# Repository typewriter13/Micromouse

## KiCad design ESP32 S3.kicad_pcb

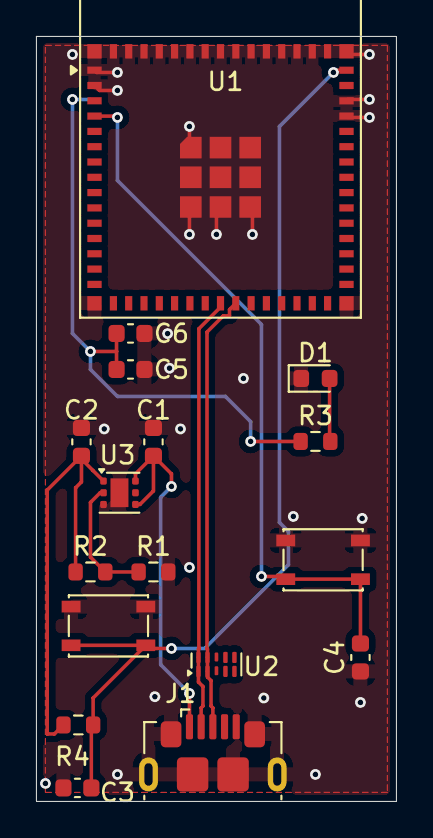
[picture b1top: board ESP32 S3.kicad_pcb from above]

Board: 2 copper layers, 20.0 x 42.5 mm, 17 parts (0 on the bottom side), 9 nets.

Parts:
C1, C2, C6: 10uF; C_0603_1608Metric
C3, C4, C5: 0.1uF; C_0603_1608Metric
D1: LED; LED_0603_1608Metric
J1: USB_B_Micro; USB_Micro-B_GCT_USB3076-30-A
R1: 200K; R_0603_1608Metric
R2: 1M; R_0603_1608Metric
R3: 5.1K; R_0603_1608Metric
R4: 10K; R_0603_1608Metric
SW1: RESET; SW_SPST_PTS810
SW2: BOOT; SW_SPST_PTS810
U1: ESP32-S3-MINI-1; ESP32-S2-MINI-1
U2: D3V3XA4B10LP; Diodes_UDFN-10_1x2.5mm_P0.5mm
U3: TLV75801PDRV; WSON-6-1EP_2x2mm_P0.65mm_EP1x1.6mm

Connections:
/3V3: C2.1, C5.2, C6.1, R2.1, R3.1, R4.1, U1.3 (3V3), U3.1 (OUT)
/5VUSB: C1.1, J1.1 (VBUS), U2.4, U2.7 (NC), U3.4 (EN), U3.6 (IN)
/ESP32_EN: C3.2, R4.2, SW1.2, U1.45 (EN)
/GPIOO: C4.2, SW2.2, U1.4 (IO0)
/USB_N: J1.2 (D-), U1.23 (USB_D-), U2.1, U2.10 (NC)
/USB_P: J1.3 (D+), U1.24 (USB_D+), U2.2, U2.9 (NC)
GND: C1.2, C2.2, C3.1, C4.1, C5.1, C6.2, D1.1 (K), J1.5 (GND), J1.SH (Shield), R1.2, SW1.1, SW2.1, U1.1 (GND), U1.2 (GND), U1.42 (GND), U1.43 (GND), U1.46 (GND), U1.47 (GND), U1.48 (GND), U1.49 (GND), U1.50 (GND), U1.51 (GND), U1.52 (GND), U1.53 (GND), U1.54 (GND), U1.55 (GND), U1.56 (GND), U1.57 (GND), U1.58 (GND), U1.59 (GND), U1.60 (GND), U1.61 (GND), U1.62 (GND), U1.63 (GND), U1.64 (GND), U1.65 (GND), U2.3 (VSS), U2.8 (VSS), U3.3 (GND), U3.7 (GND)
unnamed: D1.2 (A), R3.2
unnamed: R1.1, R2.2, U3.2 (FB)

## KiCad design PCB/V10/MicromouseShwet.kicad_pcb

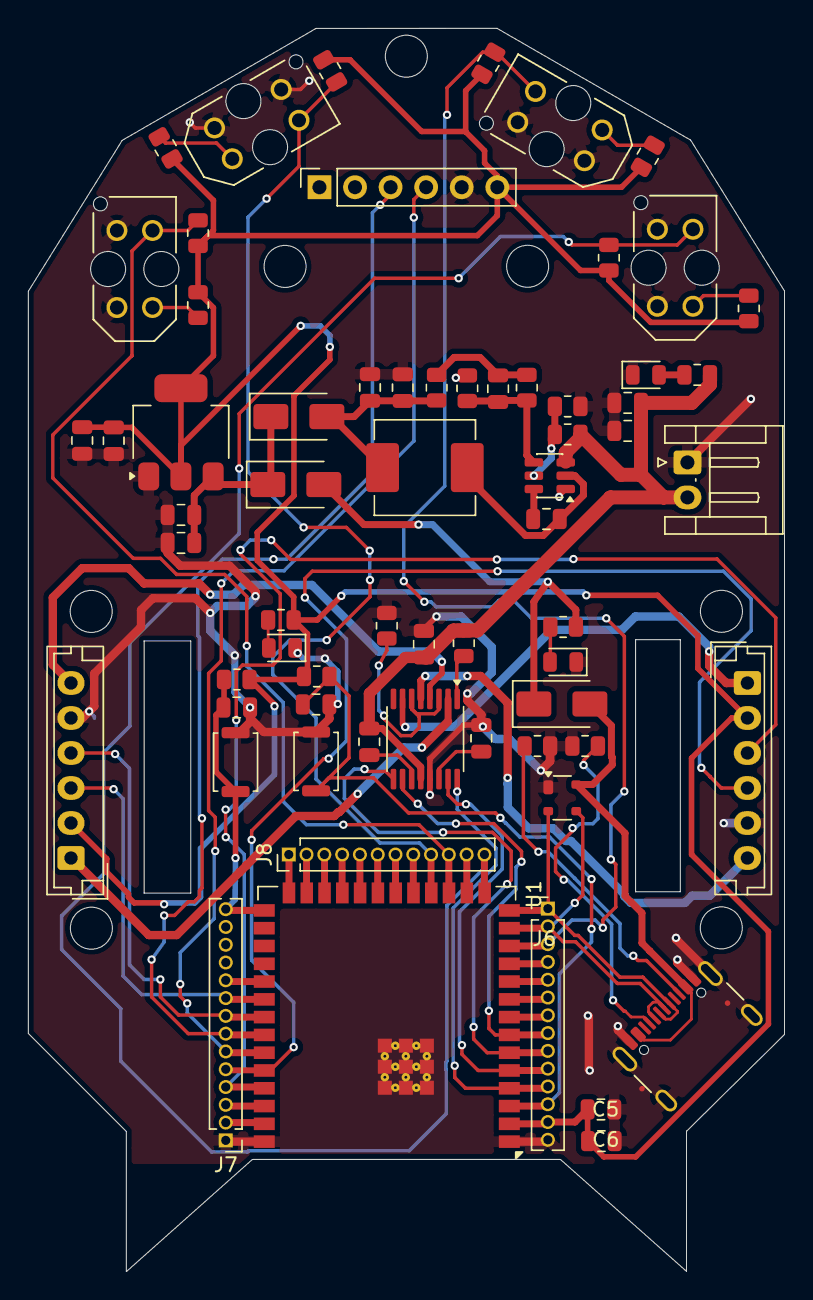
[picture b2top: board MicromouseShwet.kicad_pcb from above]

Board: 2 copper layers, 54.0 x 88.8 mm, 65 parts (0 on the bottom side), 63 nets.

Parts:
C1: 0.01uF; C_0805_2012Metric
C2: 2.2uF; C_0805_2012Metric
C3, C6, C8, C14: 10uF; C_0805_2012Metric
C4, C5, C7, C9, C10, C15, C17: 0.1uF; C_0805_2012Metric
C11, C12, C16: 22uF; C_0805_2012Metric
C13: 75pF; C_0805_2012Metric
D7: SP0503BAHT; SOT-143
D14, D17, D18: LED; LED_0805_2012Metric
D16, D19, D20: SS14; D_SMA
J1: ToF Female Socket; PinSocket_1x06_P2.54mm_Vertical
J2: Screw_Terminal_01x02; JST_EH_S2B-EH_1x02_P2.50mm_Horizontal
J5: USB_C_Receptacle_USB2.0_16P; USB_C_Receptacle_GCT_USB4105-xx-A_16P_TopMnt_Horizontal
J6, J7: Conn_01x14_Pin; PinHeader_1x14_P1.27mm_Vertical
J8: Conn_01x12_Pin; PinHeader_1x12_P1.27mm_Vertical
J10, J11: Conn_01x06_Pin; JST_EH_B6B-EH-A_1x06_P2.50mm_Vertical
L1: 10uH; L_Sunlord_MWSA0603S
R1: 200mOhm; R_0805_2012Metric
R2, R4, R9, R11: 4.7k; R_0805_2012Metric
R3, R5, R10, R12: 150R; R_0805_2012Metric
R6, R8: 5.1K; R_0805_2012Metric
R7, R20: 10K; R_0805_2012Metric
R13: 511K; R_0805_2012Metric
R14: 105K; R_0805_2012Metric
R15: 49.9K; R_0805_2012Metric
R16, R25, R26: 330R; R_0805_2012Metric
R17: 100K; R_0805_2012Metric
R18: 13.3K; R_0805_2012Metric
R27: 52.3K; R_0805_2012Metric
SW1: RESET; SW_Push_SPST_NO_Alps_SKRK
SW2: BOOT; SW_Push_SPST_NO_Alps_SKRK
U1: ESP32-S3-WROOM-2
U2: DRV8833PW; TSSOP-16_4.4x5mm_P0.65mm
U3, U7, U8, U9: TCRT5000; OPTO_TCRT5000
U5: AMS1117-3.3; SOT-223-3_TabPin2
U10: TPS54302; SOT-23-6

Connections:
/1_EEP: R27.2, U2.1 (~SLEEP)
/3V3: C5.2, C6.1, C16.1, C17.1, J1.6, J6.13, J10.2, J11.2, R2.1, R3.2, R4.1, R5.2, R7.1, R9.1, R10.2, R11.1, R12.2, R16.1, R20.1, U1.2 (3V3), U5.2 (VO)
/5V_B: C11.1, C12.1, D19.2 (A), L1.2, R15.1
/5V_USB: D16.1 (K), D20.2 (A), R26.1
/7.4V: C1.2, C3.2, C8.1, C9.1, J2.2, R13.1, R25.1, R27.1, U2.12 (VM), U10.3 (VIN)
/EN: C4.2, J6.12, R7.2, SW1.2, U1.3 (EN)
/GPIO_0: C7.2, J7.14, R20.2, SW2.2, U1.27 (IO0)
/GPIO_1: J7.2, U1.39 (IO1)
/GPIO_2: J7.3, U1.38 (IO2)
/GPIO_3: J8.12, R2.2, U1.15 (IO3), U3.COLL
/GPIO_8: J6.3, R4.2, U1.12 (IO8), U7.COLL
/GPIO_9: J8.10, R9.2, U1.17 (IO9), U8.COLL
/GPIO_10: J8.9, R11.2, U1.18 (IO10), U9.COLL
/GPIO_11: J8.8, U1.19 (IO11)
/GPIO_12: J8.7, U1.20 (IO12)
/GPIO_13: J8.6, U1.21 (IO13)
/GPIO_14: J8.5, U1.22 (IO14)
/GPIO_15: J6.7, U1.8 (IO15)
/GPIO_16: J6.6, U1.9 (IO16)
/GPIO_17: J6.5, U1.10 (IO17)
/GPIO_18: J6.4, U1.11 (IO18)
/GPIO_21: J8.4, U1.23 (IO21)
/GPIO_38: J7.10, U1.31 (IO38)
/GPIO_39: J7.9, J10.3, U1.32 (MTCK/IO39)
/GPIO_40: J7.8, J10.4, U1.33 (MTDO/IO40)
/GPIO_41: J1.3, J7.7, U1.34 (MTDI/IO41)
/GPIO_42: J1.4, J7.6, U1.35 (MTMS/IO42)
/GPIO_43: J7.4, J11.3, U1.37 (TXD0/IO43)
/GPIO_44: J7.5, J11.4, U1.36 (RXD0/IO44)
/GPIO_45: J8.1, U1.26 (IO45)
/GPIO_46: J8.11, U1.16 (IO46)
/GPIO_47: J8.3, U1.24 (IO47)
/GPIO_48: J8.2, U1.25 (IO48)
/IN1: J6.11, U1.4 (IO4), U2.16 (AIN1)
/IN2: J6.10, U1.5 (IO5), U2.15 (AIN2)
/IN3: J6.9, U1.6 (IO6), U2.9 (BIN1)
/IN4: J6.8, U1.7 (IO7), U2.10 (BIN2)
/OUT1: J10.1, U2.2 (AOUT1)
/OUT2: J10.6, U2.4 (AOUT2)
/OUT3: J11.1, U2.7 (BOUT1)
/OUT4: J11.6, U2.5 (BOUT2)
/USB_D+: D7.2 (K), J5.A6 (D+), J5.B6 (D+), J6.1, U1.14 (USB_D+/IO20)
/USB_D-: D7.3 (K), J5.A7 (D-), J5.B7 (D-), J6.2, U1.13 (USB_D-/IO19)
/VBUS: D7.4 (K), D16.2 (A), J5.A4 (VBUS), J5.A9 (VBUS), J5.B4 (VBUS), J5.B9 (VBUS)
GND: C2.2, C3.1, C4.1, C5.1, C6.2, C7.1, C8.2, C9.2, C11.2, C12.2, C14.2, C15.2, C16.2, C17.2, D7.1 (A), D14.1 (K), D17.1 (K), D18.1 (K), J1.5, J2.1, J5.A1 (GND), J5.A12 (GND), J5.B1 (GND), J5.B12 (GND), J5.SH (SHIELD), J6.14, J7.1, J10.5, J11.5, R1.2, R6.2, R8.2, R14.2, R18.2, SW1.1, SW2.1, U1.1 (GND), U1.40 (GND), U1.41 (GND), U2.13 (GND), U3.CATH, U3.E, U5.1 (GND), U7.CATH, U7.E, U8.CATH, U8.E, U9.CATH, U9.E, U10.1 (GND)
unnamed: C13.1, R15.2, R17.1
unnamed: D14.2 (A), R16.2
unnamed: D17.2 (A), R25.2
unnamed: D18.2 (A), R26.2
unnamed: C14.1, C15.1, D19.1 (K), D20.1 (K), U5.3 (VI)
unnamed: J5.A5 (CC1), R6.1
unnamed: J5.B5 (CC2), R8.1
unnamed: R3.1, U3.A
unnamed: R5.1, U7.A
unnamed: R10.1, U8.A
unnamed: R12.1, U9.A
unnamed: R1.1, U2.3 (AISEN), U2.6 (BISEN)
unnamed: C1.1, U2.11 (VCP)
unnamed: C2.1, U2.14 (VINT)
unnamed: C10.1, U10.6 (BOOT)
unnamed: R13.2, R14.1, U10.5 (EN)
unnamed: C13.2, R17.2, R18.1, U10.4 (FB)
unnamed: C10.2, L1.1, U10.2 (SW)

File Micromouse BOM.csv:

"Reference","Qty","Value","DNP","Exclude from BOM","Exclude from Board","Footprint","Datasheet"
"C1","1","0.01uF","","","","Capacitor_SMD:C_0805_2012Metric","https://robu.in/product/c0805c103k3ractu-kemet-smd-multilaye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"
"C2","1","2.2uF","","","","Capacitor_SMD:C_0805_2012Metric","https://robu.in/product/c2012x7r1h225k125ae-tdk-smd-multilay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"
"C3,C6,C8,C14","4","10uF","","","","Capacitor_SMD:C_0805_2012Metric","https://evelta.com/10uf-25v-10-x7r-0805-mlcc-multilayer-cera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"
"C4,C5,C7,C9,C10,C15,C17","7","0.1uF","","","","Capacitor_SMD:C_0805_2012Metric","https://robu.in/product/c0805c104k1ractu-kemet-smd-multilaye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"
"C11,C12,C16","3","22uF","","","","Capacitor_SMD:C_0805_2012Metric","https://www.ktron.in/product/22uf-25v-ceramic-capacitor-smd-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"
"C13","1","75pF","","","","Capacitor_SMD:C_0805_2012Metric","https://robu.in/product/tcc0805cog750j500bt-cctc-smt-ceramic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"
"D7","1","SP0503BAHT","","","","Package_TO_SOT_SMD:SOT-143","https://robu.in/product/sp0503bahtg-littelfuse-sp0503bahtg-e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"
"D14,D17,D18","3","LED","","","","LED_SMD:LED_0805_2012Metric","https://robu.in/product/17-21-g6c-ap1q1b-3t-everlight-yellow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"
"D16,D19,D20","3","SS14","","","","Diode_SMD:D_SMA","https://robu.in/product/ss14-slkor-40v-550mv1a-1a-smado-214a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"
"J1","1","ToF Female Socket","","","","Connector_PinSocket_2.54mm:PinSocket_1x06_P2.54mm_Vertical","https://robu.in/product/6-pin-female-11mm-tall-stackable-hea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"
"J2","1","Screw_Terminal_01x02","","","","Connector_JST:JST_EH_S2B-EH_1x02_P2.50mm_Horizontal","https://robu.in/product/2-pin-2-54mm-pitch-pluggable-screw-t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"
"J5","1","USB_C_Receptacle_USB2.0_16P","","","","Connector_USB:USB_C_Receptacle_GCT_USB4105-xx-A_16P_TopMnt_Horizontal","https://evelta.com/usb-type-c-receptacle-vertical-mount-usb-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"
"J6,J7","2","Conn_01x14_Pin","","","","Connector_PinHeader_1.27mm:PinHeader_1x14_P1.27mm_Vertical","https://robu.in/product/1-27mm-1x40-pin-male-single-row-head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"
"J8","1","Conn_01x12_Pin","","","","Connector_PinHeader_1.27mm:PinHeader_1x12_P1.27mm_Vertical","https://robu.in/product/1-27mm-1x40-pin-male-single-row-head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"
"J10,J11","2","Conn_01x06_Pin","","","","Connector_JST:JST_ZH_B6B-ZR_1x06_P1.50mm_Vertical","https://robu.in/product/b6b-xh-alfsn-jst-1x6p-6p-xh-tin-6-25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"
"L1","1","10uH","","","","Inductor_SMD:L_Sunlord_MWSA0603S","https://robu.in/product/mwsa0603s-100mt-sunlord-10uh-5-2a-20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"
"R1","1","200mOhm","","","","Resistor_SMD:R_0805_2012Metric","https://evelta.com/200e-5-0805-smd-resistor-royal-ohm-0805s8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"
"R2,R4,R9,R11","4","4.7k","","","","Resistor_SMD:R_0805_2012Metric","https://robu.in/product/wr08x472jtl-walsin-125mw-thick-film-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"
"R3,R5,R10,R12","4","150R","","","","Resistor_SMD:R_0805_2012Metric","https://robu.in/product/ac0805fr-07150rl-yageo-res-thick-fil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"
"R6,R8","2","5.1K","","","","Resistor_SMD:R_0805_2012Metric","https://robu.in/product/erj6geyj512v-panasonic-125mw-thick-f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"
"R7,R20","2","10K","","","","Resistor_SMD:R_0805_2012Metric","https://robu.in/product/ac0805fr-0710kl-yageo-res-thick-film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"
"R13","1","511K","","","","Resistor_SMD:R_0805_2012Metric","https://robu.in/product/ac0805fr-07511kl-yageo-125mw-thick-f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"
"R14","1","105K","","","","Resistor_SMD:R_0805_2012Metric","https://robu.in/product/rc0805fr-07105kl-yageo-125mw-thick-f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"
"R15","1","49.9K","","","","Resistor_SMD:R_0805_2012Metric","https://robu.in/product/crcw080549k9fkea-vishay-intertech-12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"
"R16,R25,R26","3","330R","","","","Resistor_SMD:R_0805_2012Metric","https://robu.in/product/rc0805fr-07330rl-yageo-res-thick-fil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"
"R17","1","100K","","","","Resistor_SMD:R_0805_2012Metric","https://robu.in/product/ac0805fr-7w100kl-yageo-res-thick-fil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"
"R18","1","13.3K","","","","Resistor_SMD:R_0805_2012Metric","https://robu.in/product/rc0805fr-0713k3l-yageo-125mw-thick-f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"
"R27","1","52.3K","","","","Resistor_SMD:R_0805_2012Metric","https://robu.in/product/ac0805fr-0752k3l-yageo-125mw-thick-f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"
"SW1","1","RESET","","","","Button_Switch_SMD:SW_Push_SPST_NO_Alps_SKRK","https://www.ktron.in/product/3x4x2mm-smd-tactile-switch/?srs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"
"SW2","1","BOOT","","","","Button_Switch_SMD:SW_Push_SPST_NO_Alps_SKRK","https://www.ktron.in/product/3x4x2mm-smd-tactile-switch/?srs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"
"U1","1","ESP32-S3-WROOM-2","","","","RF_Module:ESP32-S3-WROOM-2","https://mou.sr/45h7VjL"
"U2","1","DRV8833PW","","","","Package_SO:TSSOP-16_4.4x5mm_P0.65mm","https://www.lioncircuits.com/parts/DRV8833PW?srsltid=AfmBOoq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"
"U3,U7,U8,U9","4","TCRT5000","","","","TCRT5000:OPTO_TCRT5000","https://robu.in/product/tcrt5000-reflective-ir-sensor-photoe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"
"U5","1","AMS1117-3.3","","","","Package_TO_SOT_SMD:SOT-223-3_TabPin2","https://evelta.com/ams1117-3-3-linear-voltage-regulator-3-3v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"
"U10","1","TPS54302","","","","Package_TO_SOT_SMD:SOT-23-6","https://robu.in/product/tps54302ddcr-texas-instruments-step-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"

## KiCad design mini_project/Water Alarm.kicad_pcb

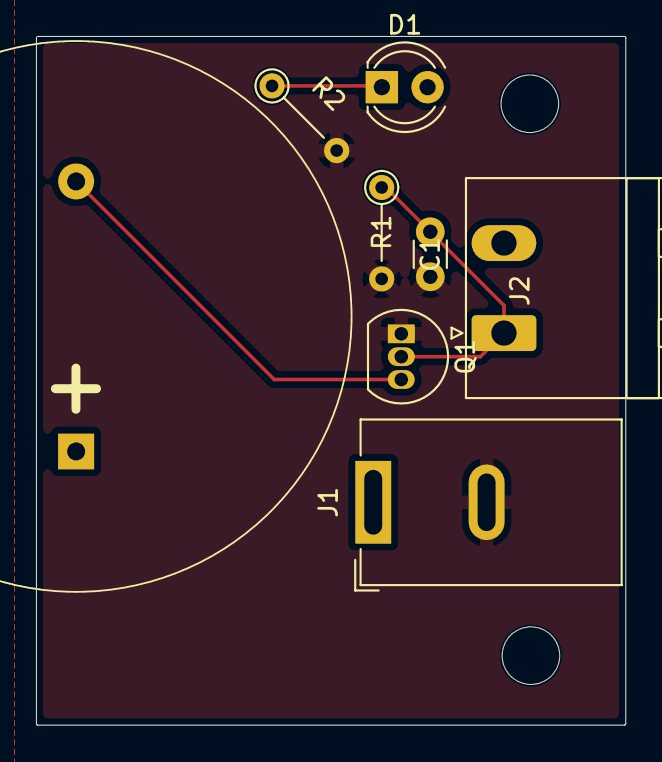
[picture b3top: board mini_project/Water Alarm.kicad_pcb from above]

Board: 2 copper layers, 32.7 x 38.3 mm, 8 parts (0 on the bottom side), 5 nets.

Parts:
BZ1: Buzzer_D30mm_H20mm_P15mm__668-1652-ND__AI-3035-TT-12V-R
C1: 1nF; C_Disc_D3.0mm_W1.6mm_P2.50mm
D1: LED_Small_Filled; LED_D4.0mm
J1: Jack-DC; BarrelJack_GCT_DCJ200-10-A_Horizontal
J2: Screw_Terminal_01x02; PhoenixContact_MSTBA_2,5_2-G_1x02_P5.00mm_Horizontal
Q1: 2N7000; TO-92_Inline
R1: 10M; R_Axial_DIN0204_L3.6mm_D1.6mm_P5.08mm_Vertical
R2: 6.8K; R_Axial_DIN0204_L3.6mm_D1.6mm_P5.08mm_Vertical

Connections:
GND: C1.2, J1.2, Q1.1 (S), R1.2, R2.2
unnamed: BZ1.2 (-), Q1.3 (D)
unnamed: D1.1 (K), R2.1
unnamed: C1.1, J2.1, Q1.2 (G), R1.1
VCC: BZ1.1 (+), D1.2 (A), J1.1, J2.2

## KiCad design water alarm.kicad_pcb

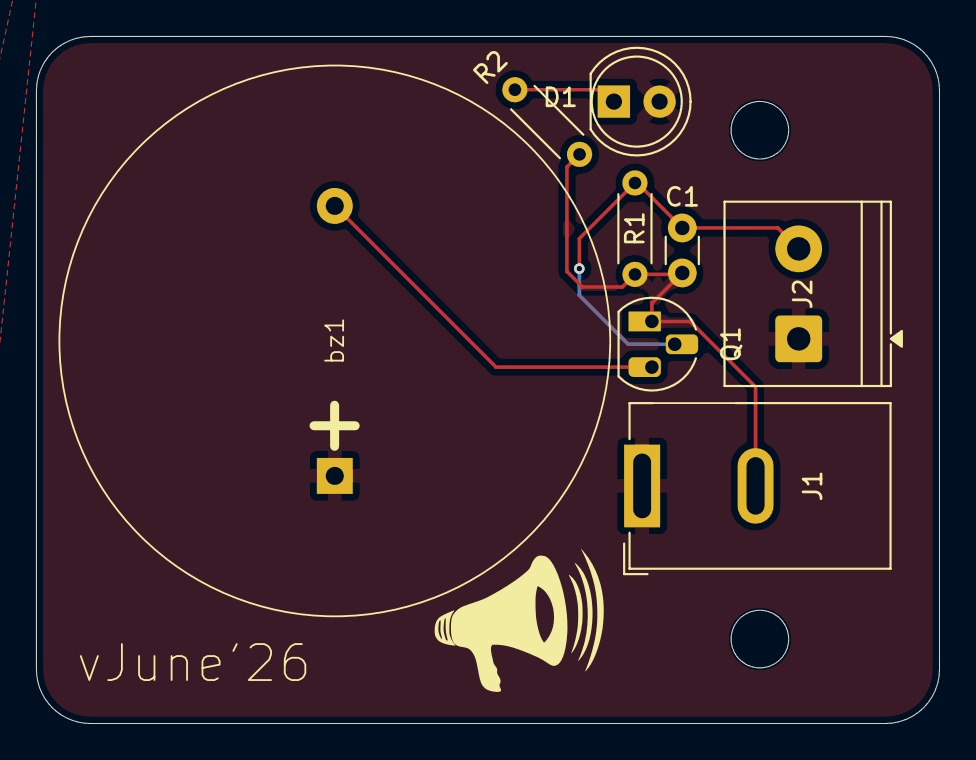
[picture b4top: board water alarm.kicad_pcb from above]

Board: 2 copper layers, 50.2 x 38.2 mm, 8 parts (0 on the bottom side), 5 nets.

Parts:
C1: 1nF; C_Disc_D3.0mm_W1.6mm_P2.50mm
D1: LED_Small_Filled; LED_D5.0mm
J1: Jack-DC; BarrelJack_GCT_DCJ200-10-A_Horizontal
J2: Screw_Terminal_01x02; TerminalBlock_Phoenix_PT-1,5-2-5.0-H_1x02_P5.00mm_Horizontal
Q1: 2N7000; TO-92_HandSolder
R1: 10M; R_Axial_DIN0204_L3.6mm_D1.6mm_P5.08mm_Horizontal
R2: 6.8K; R_Axial_DIN0204_L3.6mm_D1.6mm_P5.08mm_Horizontal
bz1: buzzer; Buzzer_D30mm_H20mm_P15mm_668-1652-ND_Al-3035-TT-12V-R

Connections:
/Gate: C1.1, J2.2, Q1.2 (G), R1.1
GND: C1.2, J1.2, Q1.1 (S), R1.2, R2.2
unnamed: D1.1 (K), R2.1
unnamed: Q1.3 (D), bz1.2 (-)
VCC: D1.2 (A), J1.1, J2.1, bz1.1 (+)
